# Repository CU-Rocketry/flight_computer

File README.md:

# flight_computer
Competition Flight Computer Module 25-26

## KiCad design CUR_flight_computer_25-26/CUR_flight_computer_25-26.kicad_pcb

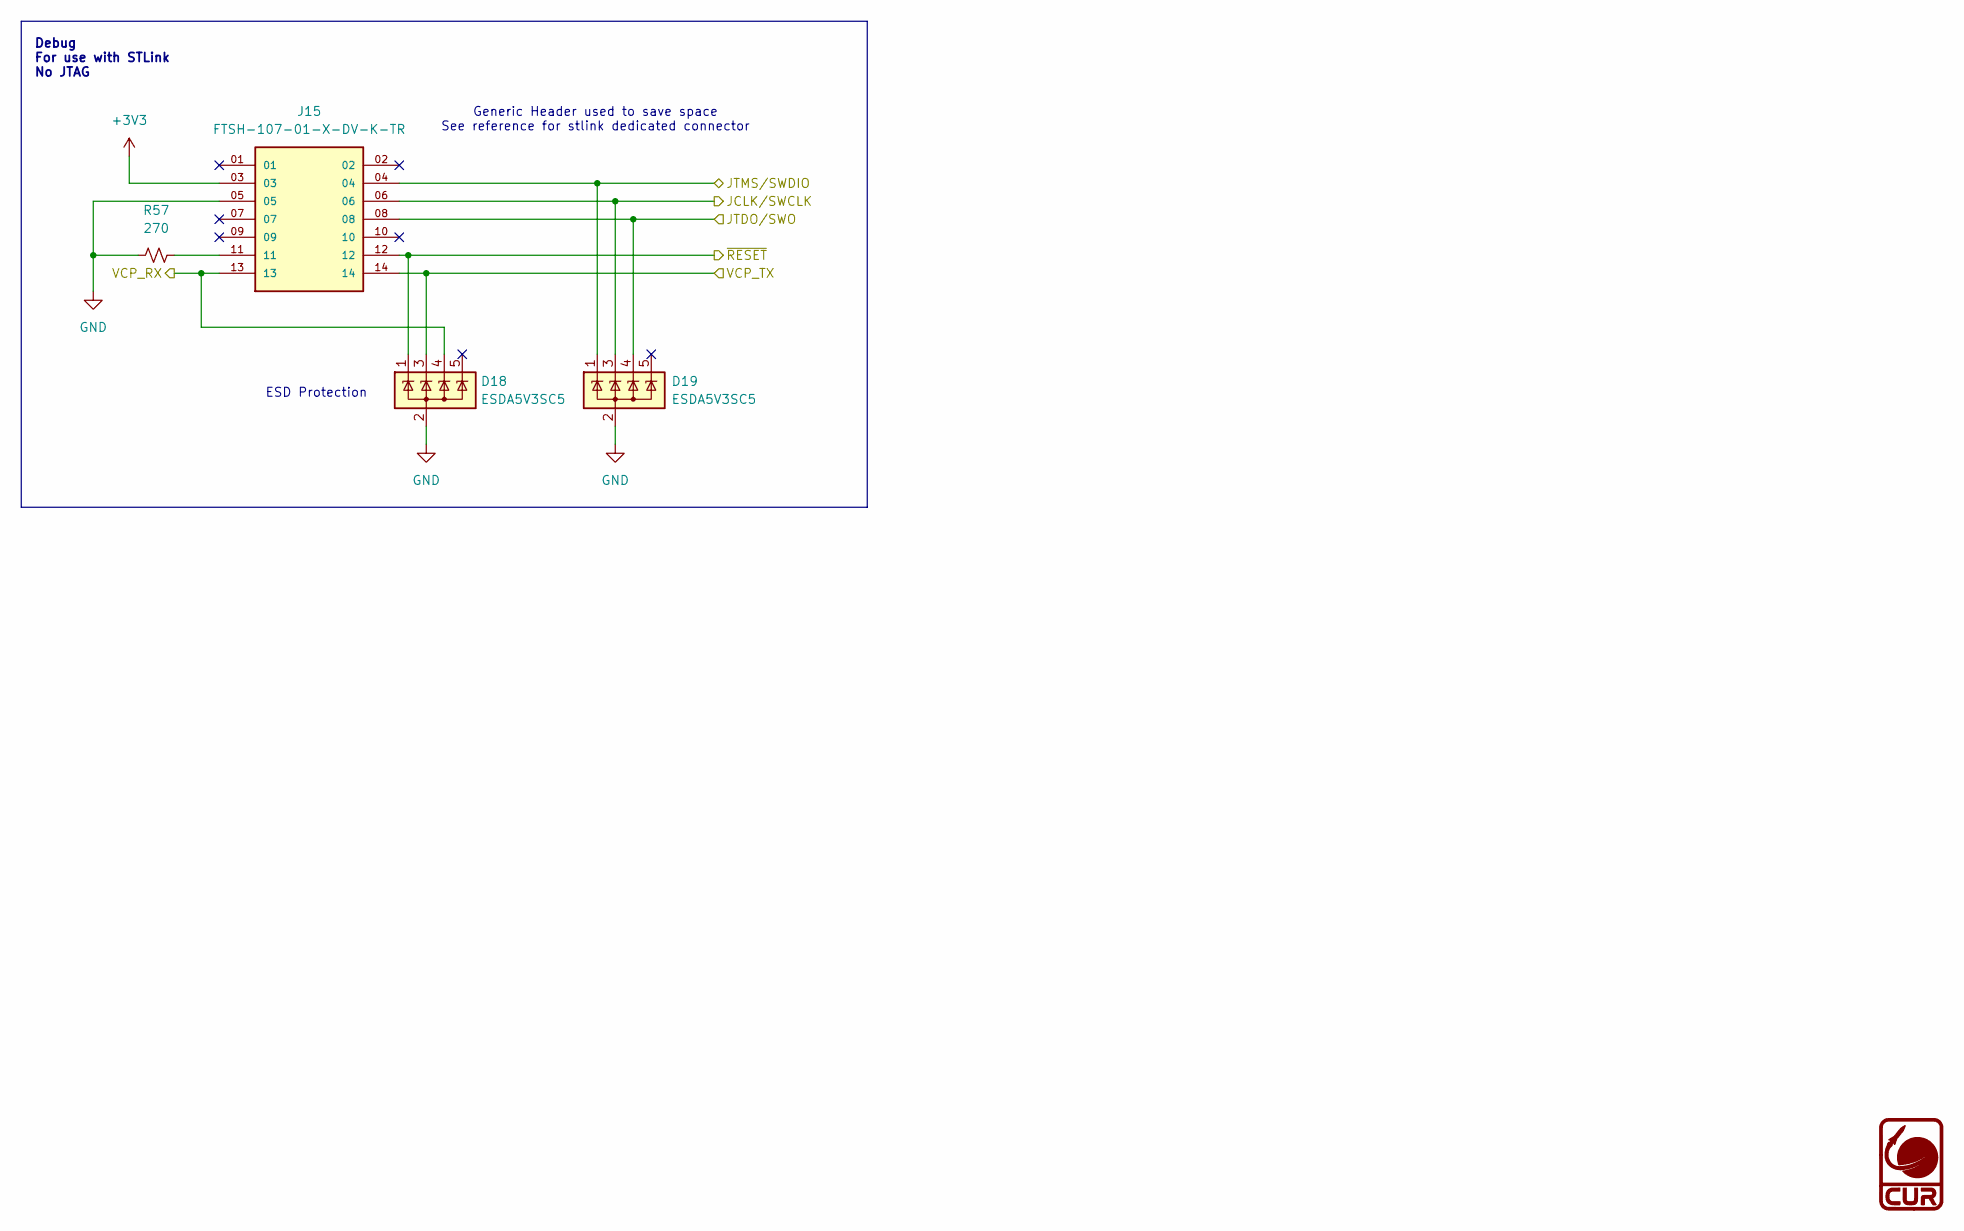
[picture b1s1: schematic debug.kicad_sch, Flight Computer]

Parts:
D18, D19: ESDA5V3SC5; SOT-23-5; MPN ESDA5V3SC5
J15: FTSH-107-01-X-DV-K-TR; SAMTEC_FTSH-107-01-X-DV-K-TR; PARTREV H
R57: 270; R_0603_1608Metric; MPN RC0603JR-07270RL

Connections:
+3V3: J15.03; also elsewhere on the board
/Debug/JCLK/SWCLK: D19.3 (K), J15.06; also elsewhere on the board
/Debug/JTDO/SWO: D19.4 (K), J15.08; also elsewhere on the board
/Debug/JTMS/SWDIO: D19.1 (K), J15.04; also elsewhere on the board
/Debug/VCP_RX: D18.4 (K), J15.13; also elsewhere on the board
/Debug/VCP_TX: D18.3 (K), J15.14; also elsewhere on the board
/MCU/NRST: D18.1 (K), J15.12; also elsewhere on the board
GND: D18.2 (A), D19.2 (A), J15.05, R57.1; also elsewhere on the board
unnamed: J15.11, R57.2

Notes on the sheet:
ESD Protection
Debug For use with STLink No JTAG
Generic Header used to save space See reference for stlink dedicated connector

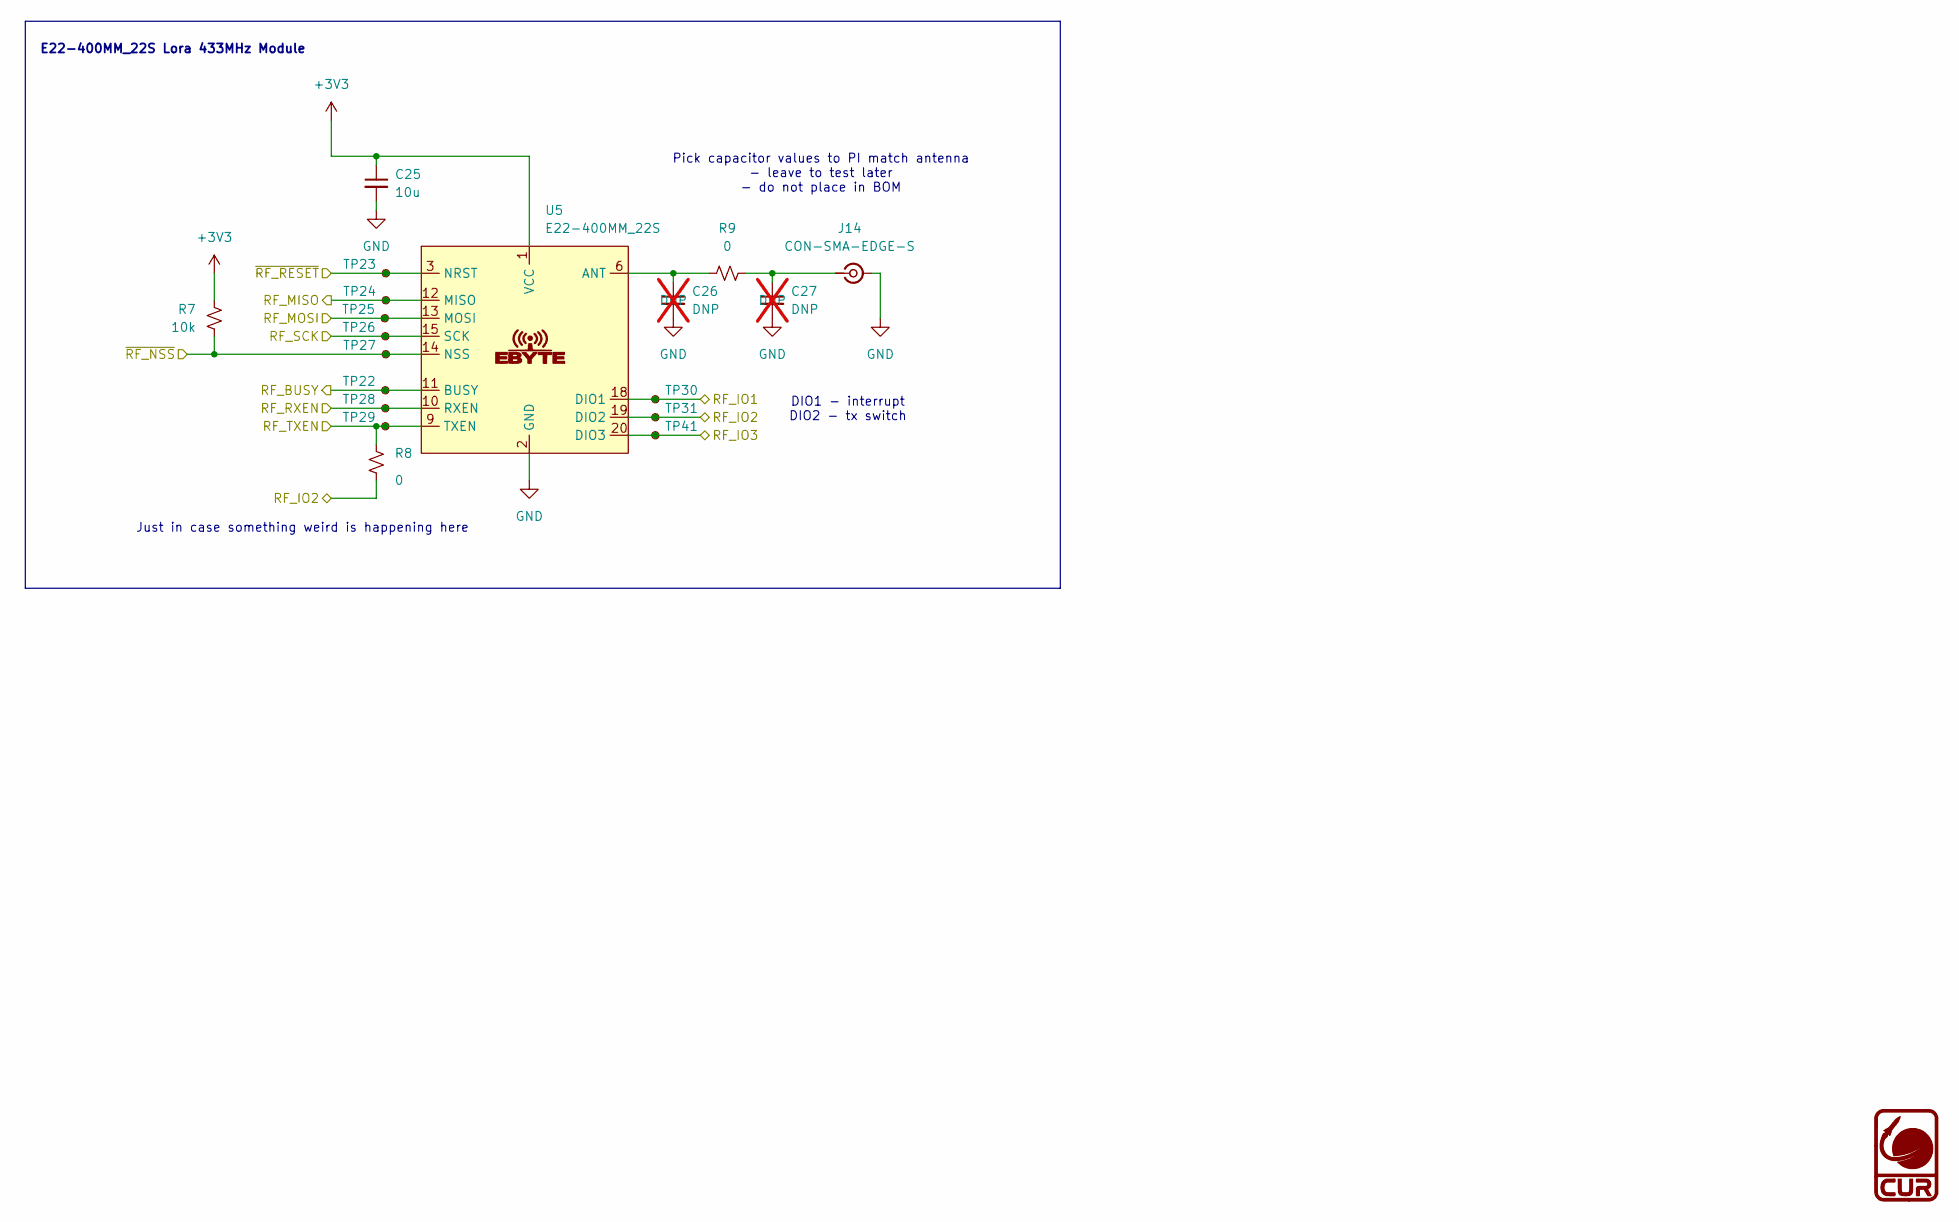
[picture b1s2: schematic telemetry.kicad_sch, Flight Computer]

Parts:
C25: 10u; C_0603_1608Metric; MPN LMK107BBJ106MALT
C26, C27: DNP; C_0603_1608Metric; MPN DNP; not fitted
J14: CON-SMA-EDGE-S; Conn_Coaxial_RFSOLUTIONS_CON-SMA-EDGE-S; MPN CON-SMA-EDGE-S
R7: 10k; R_0603_1608Metric; MPN RC0603FR-0710KL
R8, R9: 0; R_0603_1608Metric; MPN RC0603JR-070RL
TP22, TP23, TP24, TP25, TP26, TP27, TP28, TP29, TP30, TP31, TP41: RCUCTE; TestPoint_Chip_RCUCTE_0603; MPN RCUCTE
U5: E22-400MM_22S; EBYTE_LoRA_E22-400MM22S; MPN E22-400MM22S

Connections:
+3V3: C25.1, R7.1, U5.1 (VCC); also elsewhere on the board
/MCU/RF_BUSY: TP22.1, U5.11 (BUSY); also elsewhere on the board
/MCU/RF_IO1: TP30.1, U5.18 (DIO1); also elsewhere on the board
/MCU/RF_IO2: R8.2, TP31.1, U5.19 (DIO2); also elsewhere on the board
/MCU/RF_IO3: TP41.1, U5.20 (DIO3); also elsewhere on the board
/MCU/RF_MISO: TP24.1, U5.12 (MISO); also elsewhere on the board
/MCU/RF_MOSI: TP25.1, U5.13 (MOSI); also elsewhere on the board
/MCU/RF_RXEN: TP28.1, U5.10 (RXEN); also elsewhere on the board
/MCU/RF_SCK: TP26.1, U5.15 (SCK); also elsewhere on the board
/MCU/RF_TXEN: R8.1, TP29.1, U5.9 (TXEN); also elsewhere on the board
/MCU/~RF_NSS: R7.2, TP27.1, U5.14 (NSS); also elsewhere on the board
/MCU/~RF_RESET: TP23.1, U5.3 (NRST); also elsewhere on the board
GND: C25.2, C26.2, C27.2, J14.2 (Ext), U5.2 (GND), U5.7 (GND), U5.16 (GND); also elsewhere on the board
unnamed: C27.1, J14.1 (In), R9.1
unnamed: C26.1, R9.2, U5.6 (ANT)

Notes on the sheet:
Pick capacitor values to PI match antenna - leave to test later - do not place in BOM
Just in case something weird is happening here
E22-400MM_22S Lora 433MHz Module
DIO1 - interrupt DIO2 - tx switch

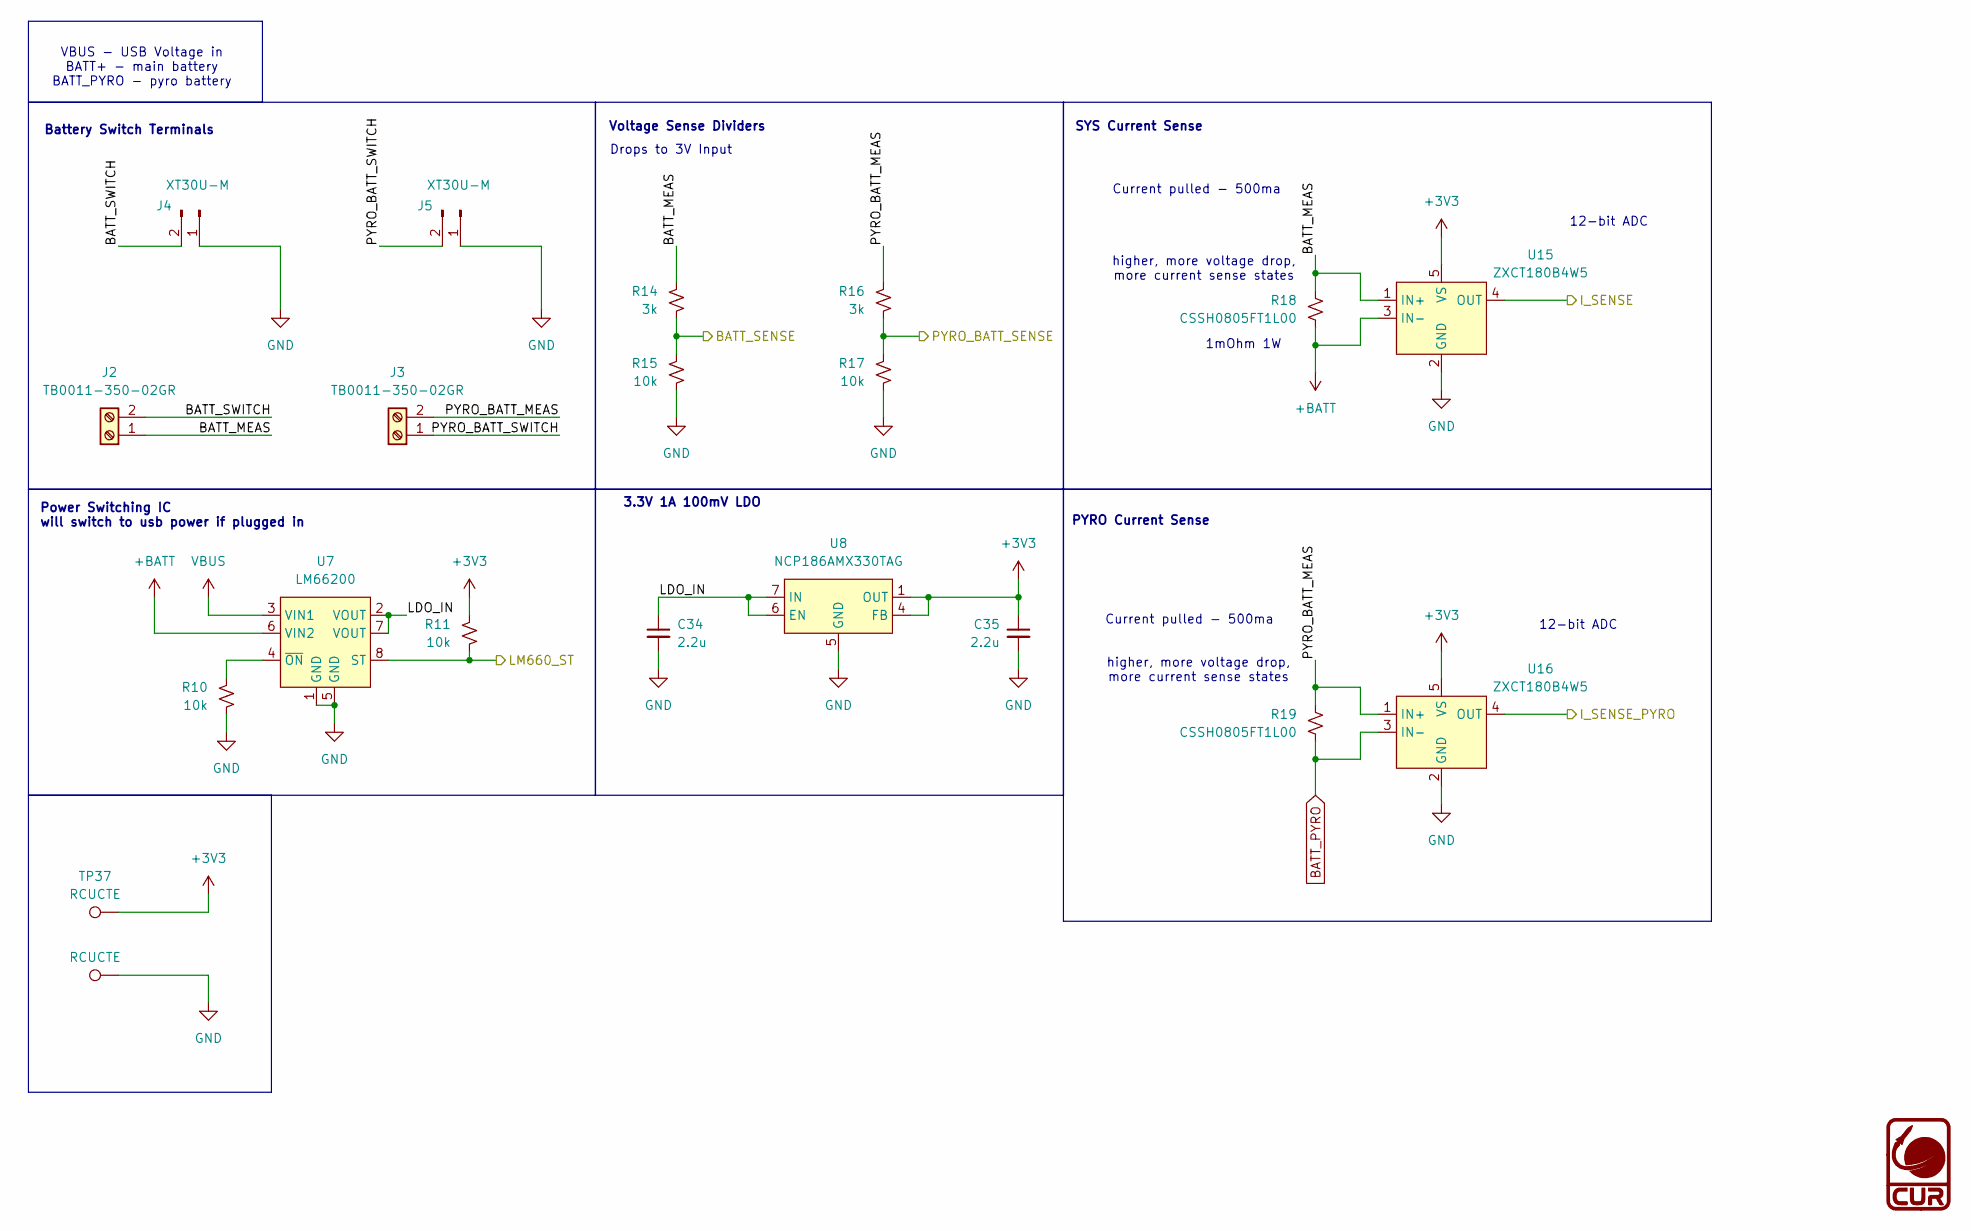
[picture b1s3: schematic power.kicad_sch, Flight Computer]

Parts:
C34, C35: 2.2u; C_0603_1608Metric; MPN CL10B225KP8NNNC
J2, J3: TB0011-350-02GR; SAMESKY_TB0011-350-02GR; MPN TB0011-350-02GR
J4, J5: XT30U-M; AMASS_XT30U-M_1x02_P5.0mm_Vertical; MPN XT30U-M
R10, R11, R15, R17: 10k; R_0603_1608Metric; MPN RC0603FR-0710KL
R14, R16: 3k; R_0603_1608Metric; MPN RC0603FR-073KL
R18, R19: CSSH0805FT1L00; R_0805_2012Metric; MPN CSSH0805FT1L00
TP37, TP40: RCUCTE; TestPoint_Chip_RCUCTE_0603; MPN RCUCTE
U7: LM66200; SOT-583-8; MPN LM66200DRLR
U8: NCP186AMX330TAG; NCP186_XDFN8_1.6x1.2mm_P0.4mm; MPN NCP186AMX330TAG
U15, U16: ZXCT180B4W5; SOT-23-5; MPN ZXCT180B4W5-7

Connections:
+3V3: C35.1, R11.2, TP37.1, U8.1 (OUT), U8.2 (OUT), U8.4 (FB), U15.5 (VS), U16.5 (VS); also elsewhere on the board
+BATT: R18.2, U7.6 (VIN2), U15.3 (IN-)
/MCU/BATT_SENSE: R14.1, R15.2; also elsewhere on the board
/MCU/I_SENSE: U15.4 (OUT); also elsewhere on the board
/MCU/I_SENSE_PYRO: U16.4 (OUT); also elsewhere on the board
/MCU/LM660_ST: R11.1, U7.8 (ST); also elsewhere on the board
/MCU/PYRO_BATT_SENSE: R16.1, R17.2; also elsewhere on the board
/Power/BATT_MEAS: J2.1, R14.2, R18.1, U15.1 (IN+)
/Power/BATT_SWITCH: J2.2, J4.2
/Power/PYRO_BATT_MEAS: J3.2, R16.2, R19.1, U16.1 (IN+)
/Power/PYRO_BATT_SWITCH: J3.1, J5.2
BATT_PYRO: R19.2, U16.3 (IN-); also elsewhere on the board
GND: C34.2, C35.2, J4.1, J5.1, R10.1, R15.1, R17.1, TP40.1, U7.1 (GND), U7.5 (GND), U8.3 (N/C), U8.5 (GND), U8.9 (EPAD), U15.2 (GND), U16.2 (GND); also elsewhere on the board
IN: C34.1, U7.2 (VOUT), U7.7 (VOUT), U8.6 (EN), U8.7 (IN), U8.8 (IN)
unnamed: R10.2, U7.4 (~ON)
VBUS: U7.3 (VIN1); also elsewhere on the board

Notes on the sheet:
Battery Switch Terminals
12-bit ADC
Current pulled - 500ma
higher, more voltage drop, more current sense states
SYS Current Sense
VBUS - USB Voltage in BATT+ - main battery BATT_PYRO - pyro battery
1mOhm 1W
Power Switching IC will switch to usb power if plugged in
3.3V 1A 100mV LDO
PYRO Current Sense
Voltage Sense Dividers
Drops to 3V Input

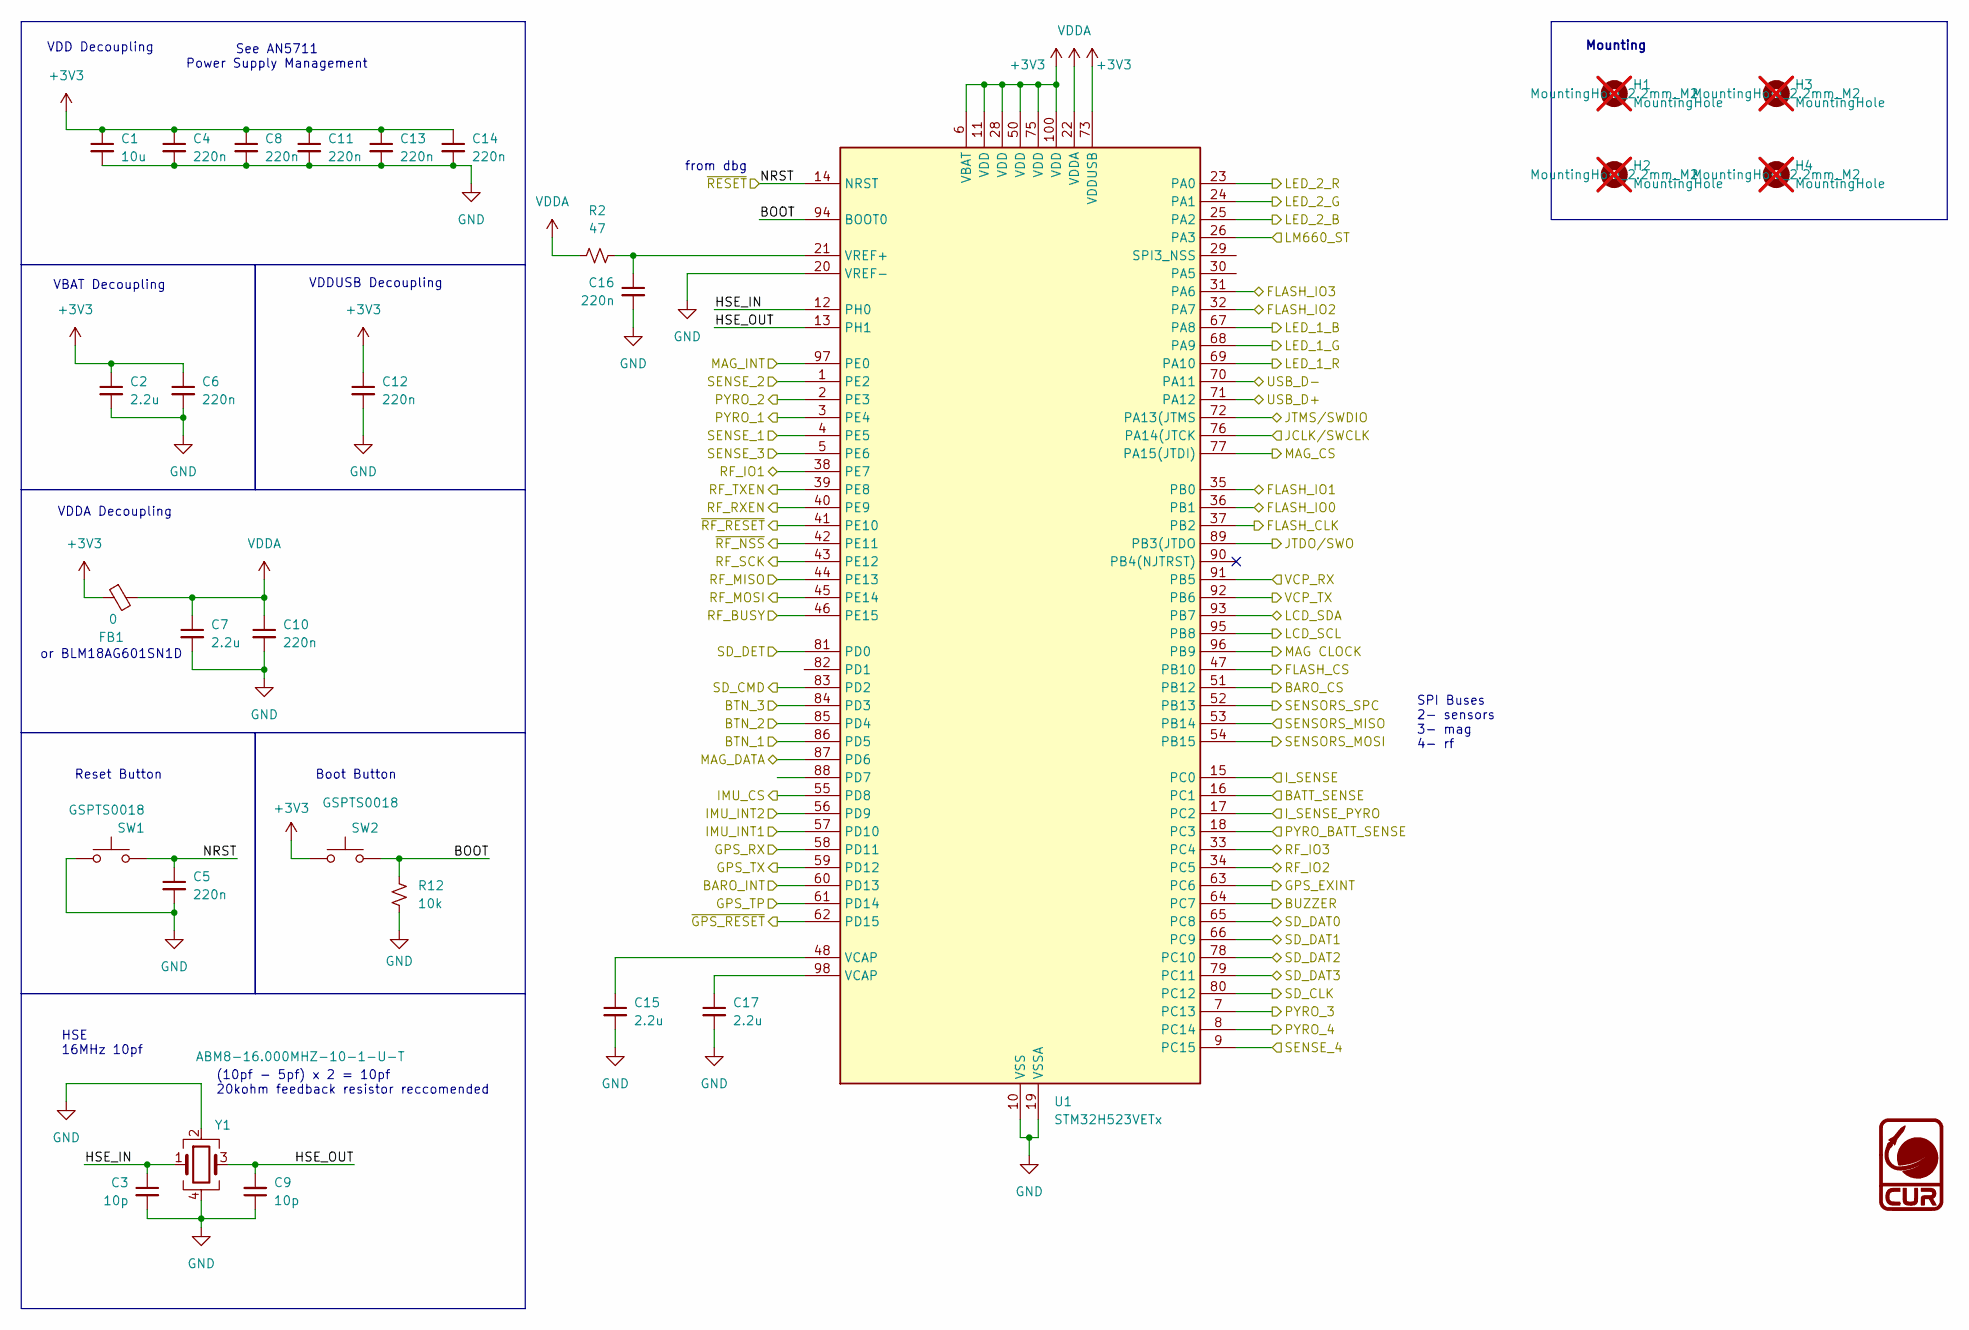
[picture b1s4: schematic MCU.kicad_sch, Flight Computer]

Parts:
C1: 10u; C_0603_1608Metric; MPN LMK107BBJ106MALT
C2, C7, C15, C17: 2.2u; C_0603_1608Metric; MPN CL10B225KP8NNNC
C3, C9: 10p; C_0603_1608Metric; MPN 0603N100J500CT
C4, C5, C6, C8, C10, C11, C12, C13, C14, C16: 220n; C_0603_1608Metric; MPN 0603B224K250CT
FB1: 0; L_0603_1608Metric; MPN RC0603JR-070RL
H1, H2, H3, H4: MountingHole; MountingHole_2.2mm_M2; MPN MountingHole_2.2mm_M2; not fitted
R2: 47; R_0603_1608Metric; MPN RC0603FR-0747RL
R12: 10k; R_0603_1608Metric; MPN RC0603FR-0710KL
SW1, SW2: GSPTS0018; SW_Push_PTS815_SJM_250_SMTR_LFS; MPN PTS815SJG250SMTR LFS
U1: STM32H523VETx; LQFP-100_14x14mm_P0.5mm; MPN STM32H523VET6
Y1: ABM8-16.000MHZ-10-1-U-T; Crystal_SMD_3225-4Pin_3.2x2.5mm; MPN ABM8-16.000MHZ-10-1-U-T

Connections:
+3V3: C1.1, C2.1, C4.1, C6.1, C8.1, C11.1, C12.1, C13.1, C14.1, FB1.1, SW2.2, U1.6 (VBAT), U1.11 (VDD), U1.28 (VDD), U1.50 (VDD), U1.73 (VDDUSB), U1.75 (VDD), U1.100 (VDD); also elsewhere on the board
/Debug/JCLK/SWCLK: U1.76 (PA14(JTCK); also elsewhere on the board
/Debug/JTDO/SWO: U1.89 (PB3(JTDO); also elsewhere on the board
/Debug/JTMS/SWDIO: U1.72 (PA13(JTMS); also elsewhere on the board
/Debug/VCP_RX: U1.91 (PB5); also elsewhere on the board
/Debug/VCP_TX: U1.92 (PB6); also elsewhere on the board
/GPS/GPS_EXINT: U1.63 (PC6); also elsewhere on the board
/GPS/GPS_RX: U1.58 (PD11); also elsewhere on the board
/GPS/GPS_TP: U1.61 (PD14); also elsewhere on the board
/GPS/GPS_TX: U1.59 (PD12); also elsewhere on the board
/GPS/~GPS_RESET: U1.62 (PD15); also elsewhere on the board
/LCD_SCL: U1.95 (PB8); also elsewhere on the board
/LCD_SDA: U1.93 (PB7); also elsewhere on the board
/MCU/BARO_CS: U1.51 (PB12); also elsewhere on the board
/MCU/BARO_INT: U1.60 (PD13); also elsewhere on the board
/MCU/BATT_SENSE: U1.16 (PC1); also elsewhere on the board
/MCU/BOOT: R12.1, SW2.1, U1.94 (BOOT0)
/MCU/BTN_1: U1.86 (PD5); also elsewhere on the board
/MCU/BTN_2: U1.85 (PD4); also elsewhere on the board
/MCU/BTN_3: U1.84 (PD3); also elsewhere on the board
/MCU/BUZZER: U1.64 (PC7); also elsewhere on the board
/MCU/FLASH_CLK: U1.37 (PB2); also elsewhere on the board
/MCU/FLASH_CS: U1.47 (PB10); also elsewhere on the board
/MCU/FLASH_IO0: U1.36 (PB1); also elsewhere on the board
/MCU/FLASH_IO1: U1.35 (PB0); also elsewhere on the board
/MCU/FLASH_IO2: U1.32 (PA7); also elsewhere on the board
/MCU/FLASH_IO3: U1.31 (PA6); also elsewhere on the board
/MCU/HSE_IN: C3.1, U1.12 (PH0), Y1.1
/MCU/HSE_OUT: C9.2, U1.13 (PH1), Y1.3
/MCU/IMU_CS: U1.55 (PD8); also elsewhere on the board
/MCU/IMU_INT1: U1.57 (PD10); also elsewhere on the board
/MCU/IMU_INT2: U1.56 (PD9); also elsewhere on the board
/MCU/I_SENSE: U1.15 (PC0); also elsewhere on the board
/MCU/I_SENSE_PYRO: U1.17 (PC2); also elsewhere on the board
/MCU/LED_1_B: U1.67 (PA8); also elsewhere on the board
/MCU/LED_1_G: U1.68 (PA9); also elsewhere on the board
/MCU/LED_1_R: U1.69 (PA10); also elsewhere on the board
/MCU/LED_2_B: U1.25 (PA2); also elsewhere on the board
/MCU/LED_2_G: U1.24 (PA1); also elsewhere on the board
/MCU/LED_2_R: U1.23 (PA0); also elsewhere on the board
/MCU/LM660_ST: U1.26 (PA3); also elsewhere on the board
/MCU/MAG CLOCK: U1.96 (PB9); also elsewhere on the board
/MCU/MAG_CS: U1.77 (PA15(JTDI)); also elsewhere on the board
/MCU/MAG_DATA: U1.87 (PD6); also elsewhere on the board
/MCU/MAG_INT: U1.97 (PE0); also elsewhere on the board
/MCU/NRST: C5.1, SW1.1, U1.14 (NRST); also elsewhere on the board
/MCU/PYRO_1: U1.3 (PE4); also elsewhere on the board
/MCU/PYRO_2: U1.2 (PE3); also elsewhere on the board
/MCU/PYRO_3: U1.7 (PC13); also elsewhere on the board
/MCU/PYRO_4: U1.8 (PC14); also elsewhere on the board
/MCU/PYRO_BATT_SENSE: U1.18 (PC3); also elsewhere on the board
/MCU/RF_BUSY: U1.46 (PE15); also elsewhere on the board
/MCU/RF_IO1: U1.38 (PE7); also elsewhere on the board
/MCU/RF_IO2: U1.34 (PC5); also elsewhere on the board
/MCU/RF_IO3: U1.33 (PC4); also elsewhere on the board
/MCU/RF_MISO: U1.44 (PE13); also elsewhere on the board
/MCU/RF_MOSI: U1.45 (PE14); also elsewhere on the board
/MCU/RF_RXEN: U1.40 (PE9); also elsewhere on the board
/MCU/RF_SCK: U1.43 (PE12); also elsewhere on the board
/MCU/RF_TXEN: U1.39 (PE8); also elsewhere on the board
/MCU/SD_CLK: U1.80 (PC12); also elsewhere on the board
/MCU/SD_CMD: U1.83 (PD2); also elsewhere on the board
/MCU/SD_DAT0: U1.65 (PC8); also elsewhere on the board
/MCU/SD_DAT1: U1.66 (PC9); also elsewhere on the board
/MCU/SD_DAT2: U1.78 (PC10); also elsewhere on the board
/MCU/SD_DAT3: U1.79 (PC11); also elsewhere on the board
/MCU/SD_DET: U1.81 (PD0); also elsewhere on the board
/MCU/SENSE_1: U1.4 (PE5); also elsewhere on the board
/MCU/SENSE_2: U1.1 (PE2); also elsewhere on the board
/MCU/SENSE_3: U1.5 (PE6); also elsewhere on the board
/MCU/SENSE_4: U1.9 (PC15); also elsewhere on the board
/MCU/USB_D+: U1.71 (PA12); also elsewhere on the board
/MCU/USB_D-: U1.70 (PA11); also elsewhere on the board
/MCU/~RF_NSS: U1.42 (PE11); also elsewhere on the board
/MCU/~RF_RESET: U1.41 (PE10); also elsewhere on the board
/Sensors/MISO: U1.53 (PB14); also elsewhere on the board
/Sensors/MOSI: U1.54 (PB15); also elsewhere on the board
/Sensors/SPC: U1.52 (PB13); also elsewhere on the board
GND: C1.2, C2.2, C3.2, C4.2, C5.2, C6.2, C7.2, C8.2, C9.1, C10.2, C11.2, C12.2, C13.2, C14.2, C15.2, C16.2, C17.2, R12.2, SW1.2, U1.10 (VSS), U1.19 (VSSA), U1.20 (VREF-), U1.27 (VSS), U1.49 (VSS), U1.74 (VSS), U1.99 (VSS), Y1.2, Y1.4; also elsewhere on the board
unnamed: C15.1, U1.48 (VCAP)
unnamed: C17.1, U1.98 (VCAP)
unnamed: C16.1, R2.2, U1.21 (VREF+)
VDDA: C7.1, C10.1, FB1.2, R2.1, U1.22 (VDDA)

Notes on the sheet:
VDD Decoupling
VBAT Decoupling
VDDUSB Decoupling
VDDA Decoupling
Mounting
(10pf - 5pf) x 2 = 10pf 20kohm feedback resistor reccomended
Boot Button
or BLM18AG601SN1D
Reset Button
SPI Buses 2- sensors 3- mag 4- rf
HSE 16MHz 10pf
See AN5711 Power Supply Management
from dbg

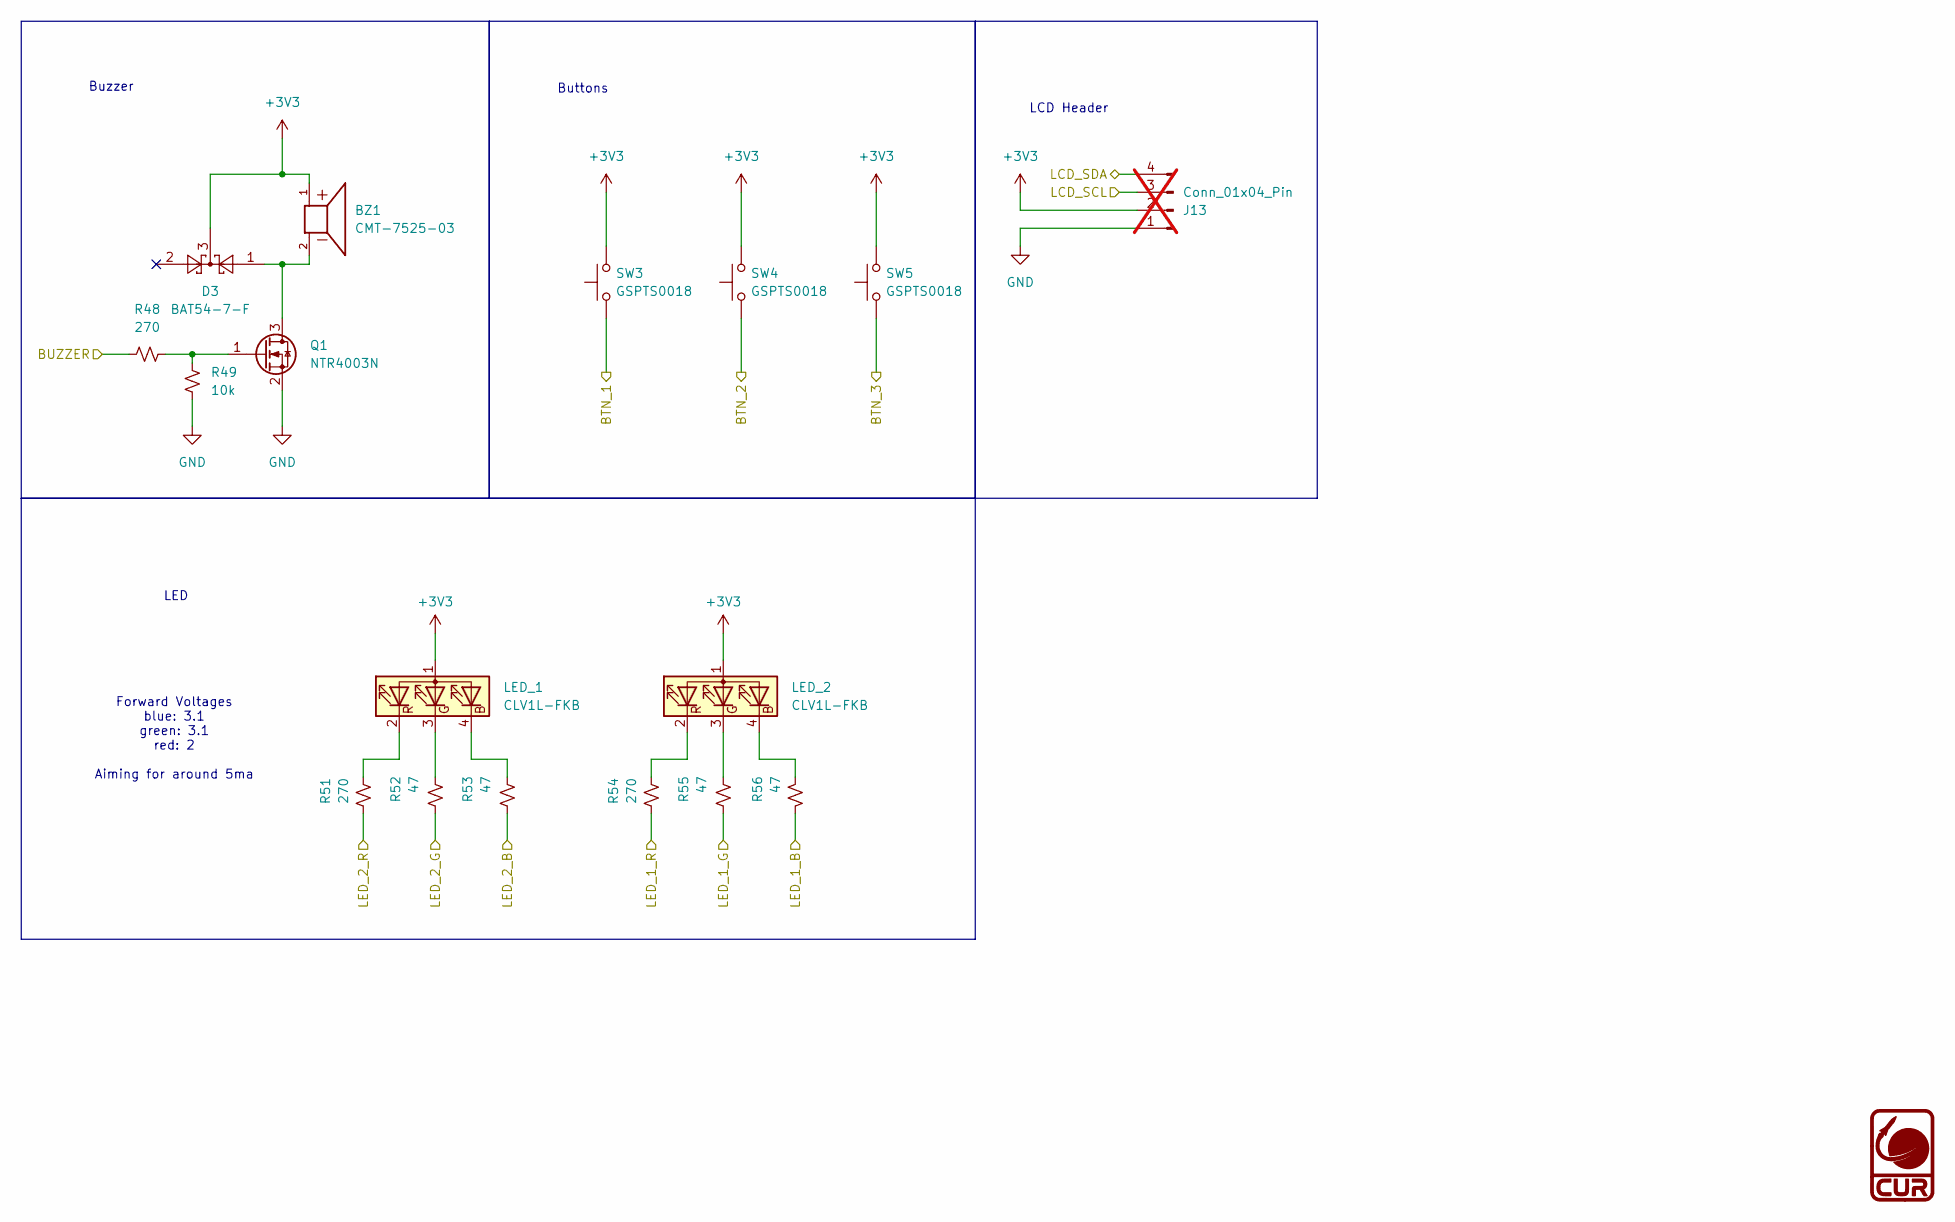
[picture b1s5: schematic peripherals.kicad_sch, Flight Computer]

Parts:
BZ1: CMT-7525-03; XDCR_CMT-7525-03-SMT-TR; PARTREV 1.0
D3: BAT54-7-F; SOT-23; MPN BAT54-7-F
J13: Conn_01x04_Pin; PinHeader_1x04_P2.54mm_Vertical; MPN PinHeader_2.54mm; not fitted
LED_1, LED_2: CLV1L-FKB; LED_Cree-PLCC4_3.2x2.8mm_CCW; MPN CLV1L-FKB-CJQRNQEFGBB79353
Q1: NTR4003N; SOT-23; MPN NTR4003N
R48, R51, R54: 270; R_0603_1608Metric; MPN RC0603JR-07270RL
R49: 10k; R_0603_1608Metric; MPN RC0603FR-0710KL
R52, R53, R55, R56: 47; R_0603_1608Metric; MPN RC0603FR-0747RL
SW3, SW4, SW5: GSPTS0018; SW_Push_PTS815_SJM_250_SMTR_LFS; MPN PTS815SJG250SMTR LFS

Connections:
+3V3: BZ1.1, D3.3, J13.2, LED_1.1 (A), LED_2.1 (A), SW3.2, SW4.2, SW5.2; also elsewhere on the board
/LCD_SCL: J13.3; also elsewhere on the board
/LCD_SDA: J13.4; also elsewhere on the board
/MCU/BTN_1: SW3.1; also elsewhere on the board
/MCU/BTN_2: SW4.1; also elsewhere on the board
/MCU/BTN_3: SW5.1; also elsewhere on the board
/MCU/BUZZER: R48.1; also elsewhere on the board
/MCU/LED_1_B: R56.2; also elsewhere on the board
/MCU/LED_1_G: R55.2; also elsewhere on the board
/MCU/LED_1_R: R54.2; also elsewhere on the board
/MCU/LED_2_B: R53.2; also elsewhere on the board
/MCU/LED_2_G: R52.2; also elsewhere on the board
/MCU/LED_2_R: R51.2; also elsewhere on the board
GND: J13.1, Q1.2 (S), R49.2; also elsewhere on the board
unnamed: BZ1.2, D3.1, Q1.3 (D)
unnamed: Q1.1 (G), R48.2, R49.1

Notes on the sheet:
LCD Header
Buzzer
LED
Forward Voltages blue: 3.1 green: 3.1 red: 2 Aiming for around 5ma
Buttons

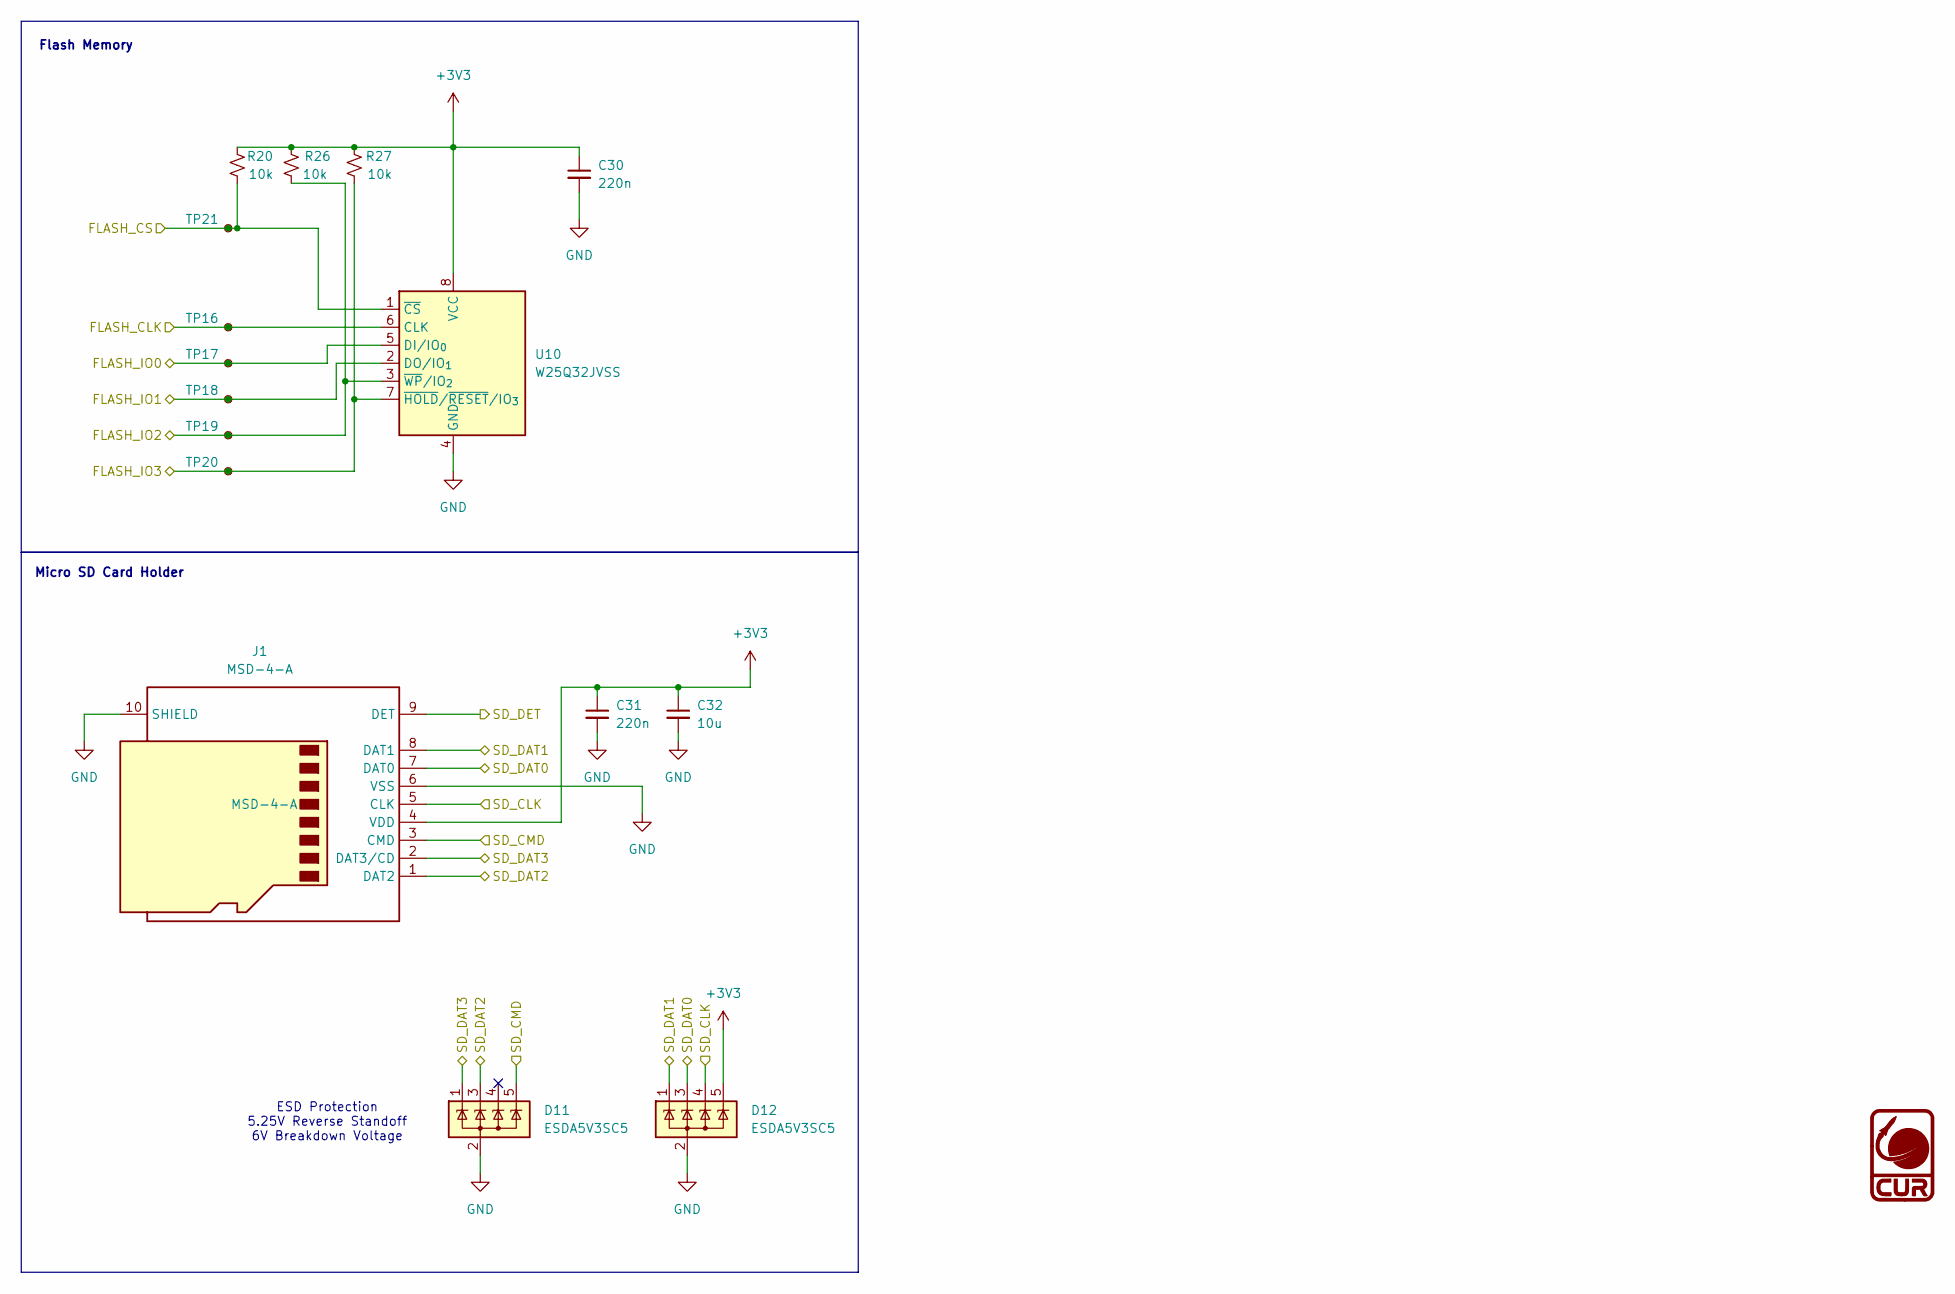
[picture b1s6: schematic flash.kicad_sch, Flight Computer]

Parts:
C30, C31: 220n; C_0603_1608Metric; MPN 0603B224K250CT
C32: 10u; C_0603_1608Metric; MPN LMK107BBJ106MALT
D11, D12: ESDA5V3SC5; SOT-23-5; MPN ESDA5V3SC5
J1: MSD-4-A; CUI_MSD-4-A; MPN MSD-4-A
R20, R26, R27: 10k; R_0603_1608Metric; MPN RC0603FR-0710KL
TP16, TP17, TP18, TP19, TP20, TP21: RCUCTE; TestPoint_Chip_RCUCTE_0603; MPN RCUCTE
U10: W25Q32JVSS; SOIC-8_5.3x5.3mm_P1.27mm; MPN BY25Q128ESSIG(T)

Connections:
+3V3: C30.1, C31.1, C32.1, D12.5 (K), J1.4 (VDD), R20.1, R26.1, R27.1, U10.8 (VCC); also elsewhere on the board
/MCU/FLASH_CLK: TP16.1, U10.6 (CLK); also elsewhere on the board
/MCU/FLASH_CS: R20.2, TP21.1, U10.1 (~CS); also elsewhere on the board
/MCU/FLASH_IO0: TP17.1, U10.5 (DI/IO_{0}); also elsewhere on the board
/MCU/FLASH_IO1: TP18.1, U10.2 (DO/IO_{1}); also elsewhere on the board
/MCU/FLASH_IO2: R26.2, TP19.1, U10.3 (~WP/IO_{2}); also elsewhere on the board
/MCU/FLASH_IO3: R27.2, TP20.1, U10.7 (~HOLD/~RESET/IO_{3}); also elsewhere on the board
/MCU/SD_CLK: D12.4 (K), J1.5 (CLK); also elsewhere on the board
/MCU/SD_CMD: D11.5 (K), J1.3 (CMD); also elsewhere on the board
/MCU/SD_DAT0: D12.3 (K), J1.7 (DAT0); also elsewhere on the board
/MCU/SD_DAT1: D12.1 (K), J1.8 (DAT1); also elsewhere on the board
/MCU/SD_DAT2: D11.3 (K), J1.1 (DAT2); also elsewhere on the board
/MCU/SD_DAT3: D11.1 (K), J1.2 (DAT3/CD); also elsewhere on the board
/MCU/SD_DET: J1.9 (DET); also elsewhere on the board
GND: C30.2, C31.2, C32.2, D11.2 (A), D12.2 (A), J1.6 (VSS), J1.10 (SHIELD), U10.4 (GND); also elsewhere on the board

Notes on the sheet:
ESD Protection 5.25V Reverse Standoff 6V Breakdown Voltage
Micro SD Card Holder
Flash Memory
